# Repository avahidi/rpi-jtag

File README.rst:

========
RPi-JTAG
========

.. image:: data/side.jpg
	   :alt: version 0.1 in action

Raspberry Pi IO header to JTAG IDC-20P connector, plus optional UART connectors and power indicators.

Note that JTAG pins are shared with GPIO, which you will need to re-configure in order to enable JTAG.
I use my minipi_ bootloader to do this, which gives me access to JTAG early in the boot.
But you can also do this manually from the u-boot prompt::

    mw.l 0x3F200000 0x00002000
    mw.l 0x3F200008 0x0061B0C0

license
-------

CERN OHL v1.2, because lets face it, this is rocket science ;)

see LICENSE_ for details

download
--------

The repository contains the KiCad project. There are also standalone schematics_ and gerber files for
oshpark_ and dirtypcbs_ (and itead/seeed). Note that I have only tested dirtypcbs.

.. _minipi: https://bitbucket.org/vahidi/mini-pi-bootloader
.. _oshpark: https://bitbucket.org/vahidi/rpi-jtag/raw/master/data/oshpark.zip
.. _dirtypcbs: https://bitbucket.org/vahidi/rpi-jtag/raw/master/data/dirtypcbs.zip
.. _schematics: https://bitbucket.org/vahidi/rpi-jtag/raw/master/data/schema.pdf
.. _LICENSE: https://bitbucket.org/vahidi/rpi-jtag/raw/master/LICENSE

.. image:: data/top.jpg
	   :alt: top view

.. image:: data/bottom.jpg
	   :alt: botom view

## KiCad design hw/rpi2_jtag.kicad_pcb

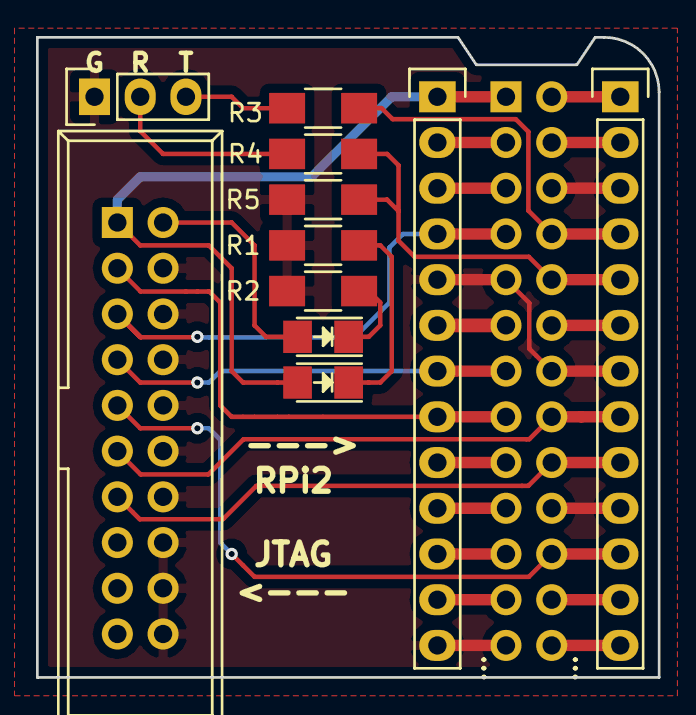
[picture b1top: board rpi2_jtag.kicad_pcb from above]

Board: 2 copper layers, 34.5 x 35.6 mm, 12 parts (1 on the bottom side), 27 nets.

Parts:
DJ1: LED; LED_1206
DPI1: LED; LED_1206
J20: CONN_02X10; IDC_Header_Straight_20pins
P1, P2: CONN_01X13; Pin_Header_Straight_1x13
PI2: CONN_02X13; Socket_Strip_Straight_2x13
R1, R2, R4: 470; R_1206_HandSoldering
R3: 100; R_1206_HandSoldering
R5: 1K; R_1206_HandSoldering
UART1: CONN_01X03; Pin_Header_Straight_1x03

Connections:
3v3: DPI1.2, J20.1, P1.1, PI2.1
5v: P2.1, PI2.2
GND: J20.4, J20.6, J20.8, J20.10, J20.12, J20.14, J20.16, J20.18, J20.20, P1.5, P1.13, P2.3, P2.7, P2.10, PI2.6, PI2.9, PI2.14, PI2.20, PI2.25, R1.1, R2.1, R5.1, UART1.1
JTAG_3v3: DJ1.2, J20.2
unnamed: DJ1.1, R2.2
unnamed: DPI1.1, R1.2
unnamed: P1.2, PI2.3
unnamed: P1.3, PI2.5
unnamed: P1.6, PI2.11
unnamed: P1.9, PI2.17
unnamed: P1.10, PI2.19
unnamed: P1.11, PI2.21
unnamed: P1.12, PI2.23
unnamed: P2.2, PI2.4
unnamed: P2.6, PI2.12
unnamed: P2.12, PI2.24
unnamed: P2.13, PI2.26
unnamed: R3.1, UART1.3
unnamed: R4.1, UART1.2
RTCK: J20.11, P2.8, PI2.16
RX0: P2.5, PI2.10, R4.2, R5.2
TCK: J20.9, P2.11, PI2.22
TDI: J20.5, P1.4, PI2.7
TDO: J20.13, P2.9, PI2.18
TMS: J20.7, P1.7, PI2.13
TX0: P2.4, PI2.8, R3.2
nTRST: J20.3, P1.8, PI2.15

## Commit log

2016-05-05 v0.2 imported from private repo
2016-05-26 v0.3: corrected RX/TX pins, added voltage divider to RX. changed JTAG connector to IDC-20 v0.x: added License and fixed missing grebers. updated README with links
2016-05-27 added text about enabling JTAG from u-boot
